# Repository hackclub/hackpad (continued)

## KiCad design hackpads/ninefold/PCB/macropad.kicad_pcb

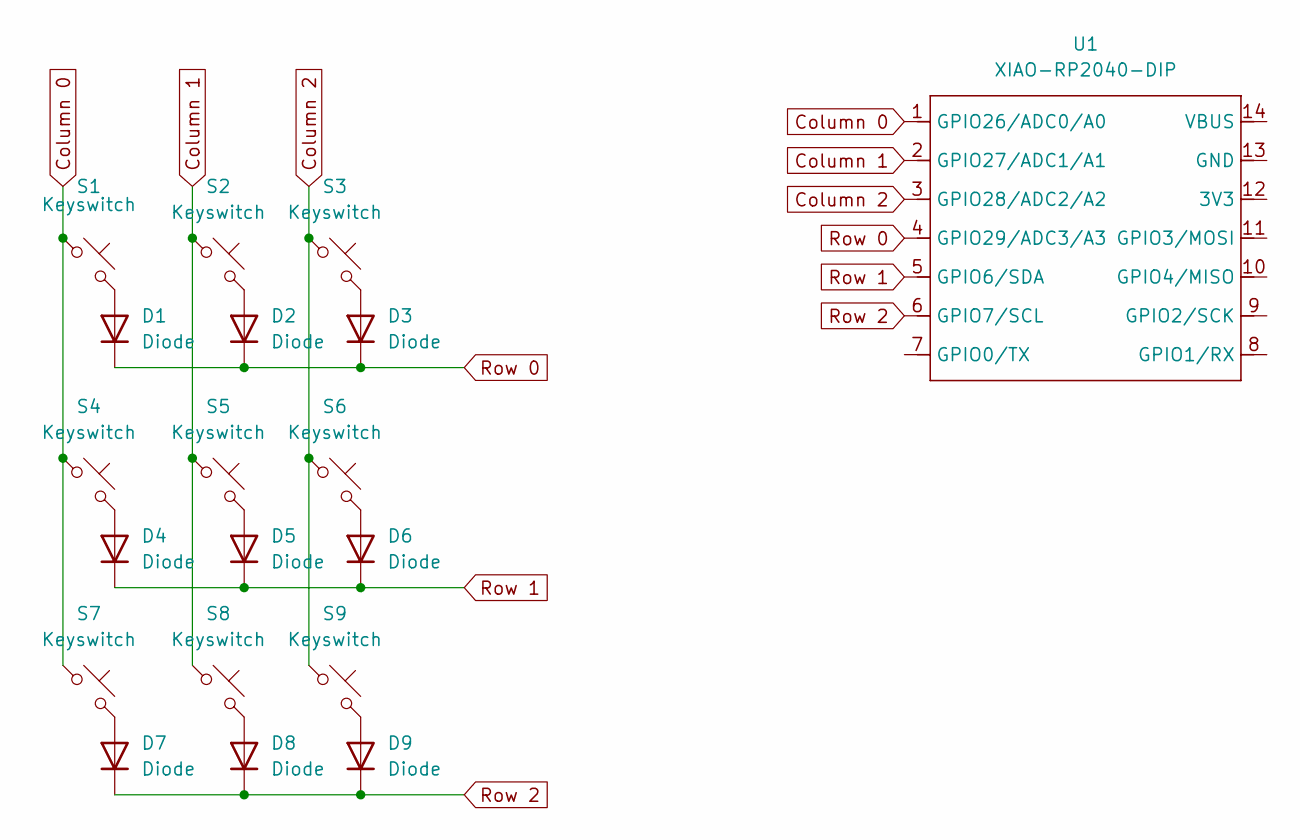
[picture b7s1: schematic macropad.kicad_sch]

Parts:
D1, D2, D3, D4, D5, D6, D7, D8, D9: Diode; Diode_DO-35
S1, S2, S3, S4, S5, S6, S7, S8, S9: Keyswitch; MX_Plate_1.00u
U1: XIAO-RP2040-DIP

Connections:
Column 0: S1.1, S4.1, S7.1, U1.1 (GPIO26/ADC0/A0)
Column 1: S2.1, S5.1, S8.1, U1.2 (GPIO27/ADC1/A1)
Column 2: S3.1, S6.1, S9.1, U1.3 (GPIO28/ADC2/A2)
unnamed: D1.2 (A), S1.2
unnamed: D2.2 (A), S2.2
unnamed: D3.2 (A), S3.2
unnamed: D4.2 (A), S4.2
unnamed: D5.2 (A), S5.2
unnamed: D6.2 (A), S6.2
unnamed: D7.2 (A), S7.2
unnamed: D8.2 (A), S8.2
unnamed: D9.2 (A), S9.2
Row 0: D1.1 (K), D2.1 (K), D3.1 (K), U1.4 (GPIO29/ADC3/A3)
Row 1: D4.1 (K), D5.1 (K), D6.1 (K), U1.5 (GPIO6/SDA)
Row 2: D7.1 (K), D8.1 (K), D9.1 (K), U1.6 (GPIO7/SCL)

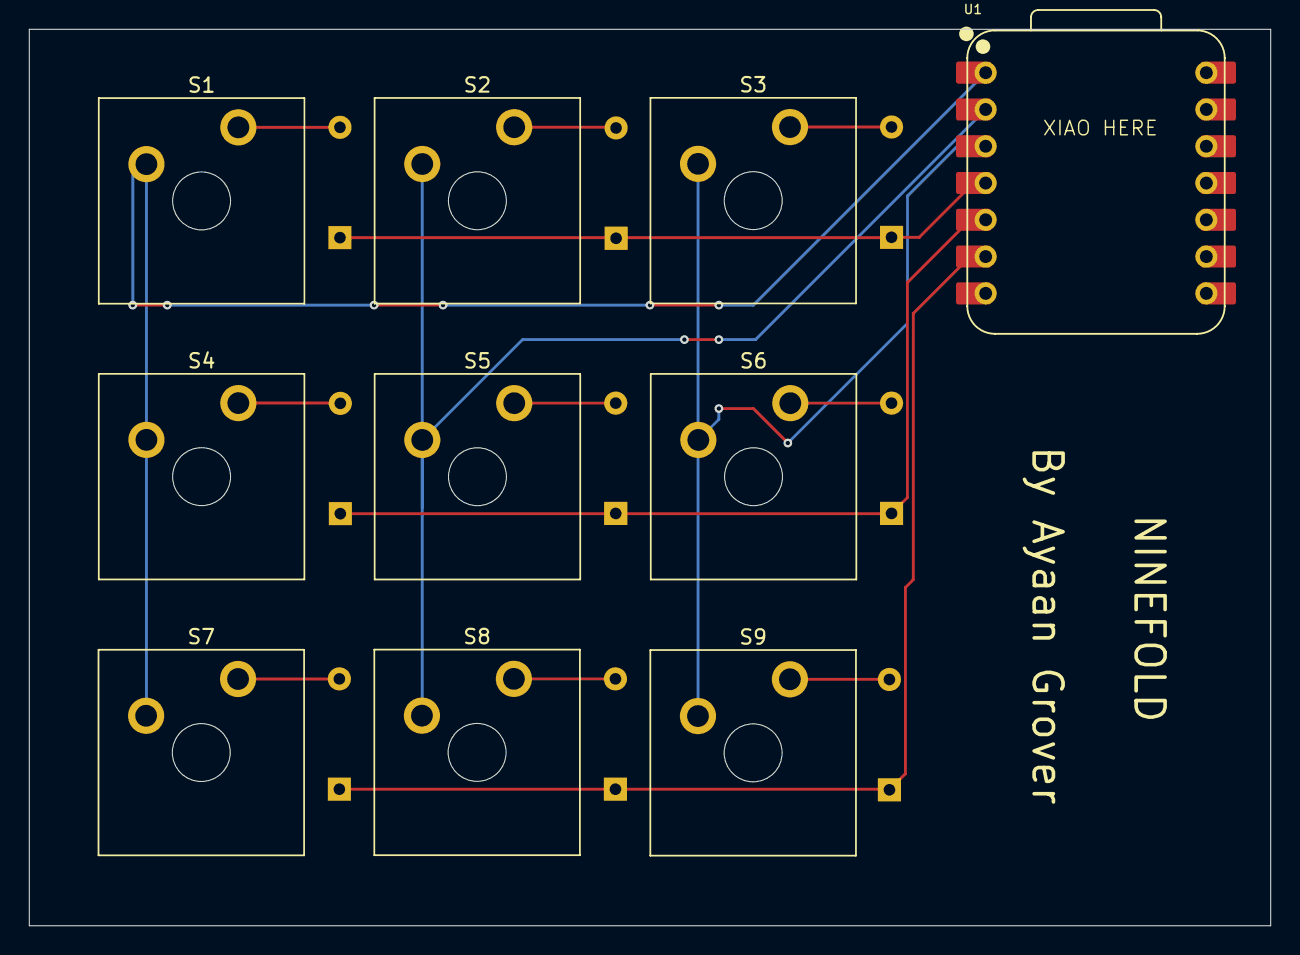
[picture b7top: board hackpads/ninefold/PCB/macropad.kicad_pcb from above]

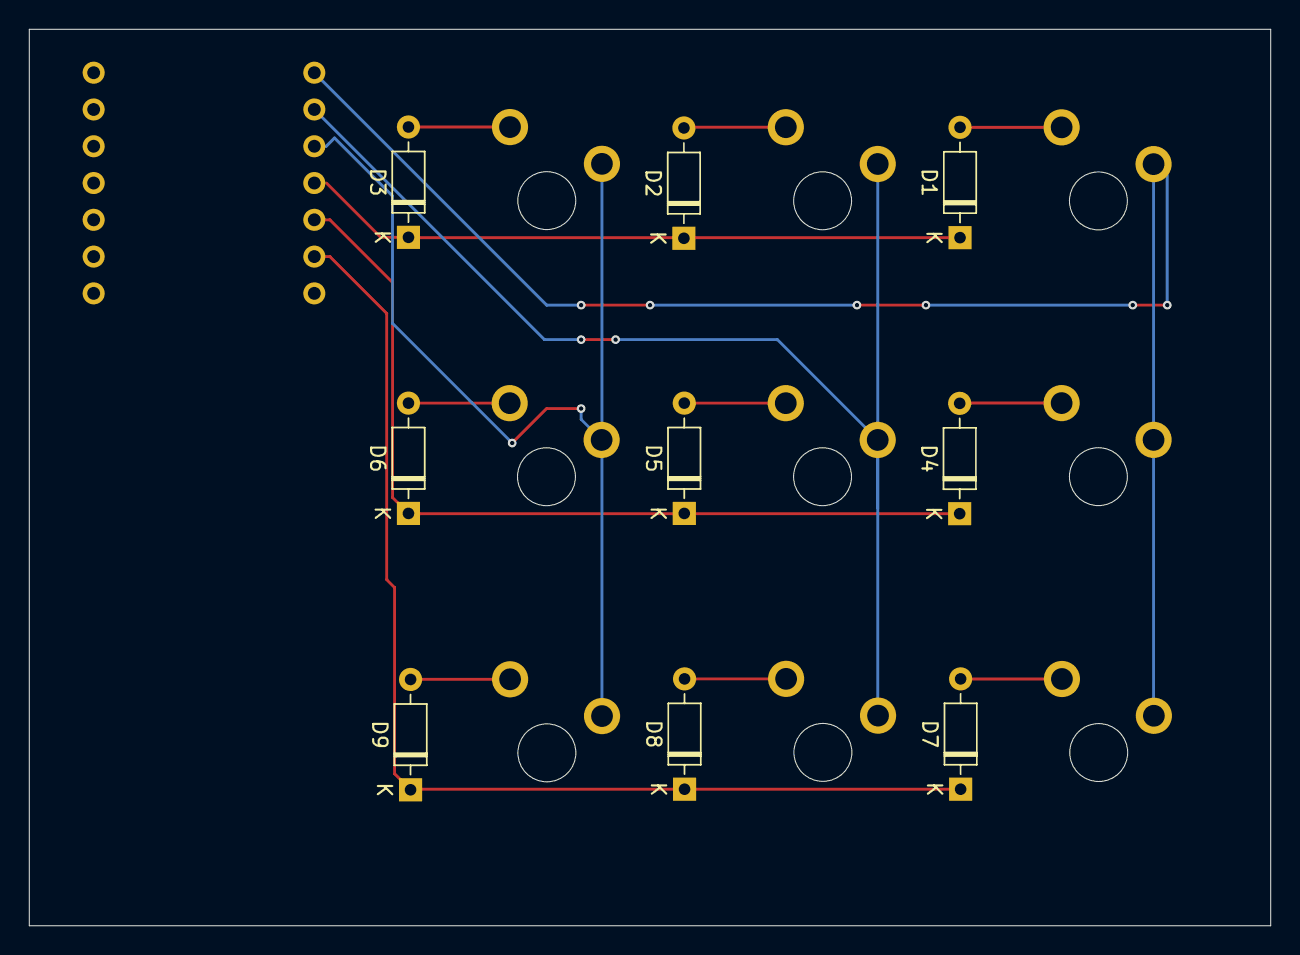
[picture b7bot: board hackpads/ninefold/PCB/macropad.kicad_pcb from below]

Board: 2 copper layers, 85.7 x 61.9 mm, 19 parts (9 on the bottom side), 15 nets.

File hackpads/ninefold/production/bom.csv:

Designator,Footprint,Quantity,Value,LCSC Part #
"D1, D2, D3, D4, D5, D6, D7, D8, D9",Diode_DO-35,9,Diode,
"S1, S2, S3, S4, S5, S6, S7, S8, S9",MX_Plate_1.00u,9,Keyswitch,
U1,XIAO-RP2040-DIP,1,XIAO-RP2040-DIP,
